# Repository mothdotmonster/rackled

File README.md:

# RACKLED

1U rackmount blinkenlights module

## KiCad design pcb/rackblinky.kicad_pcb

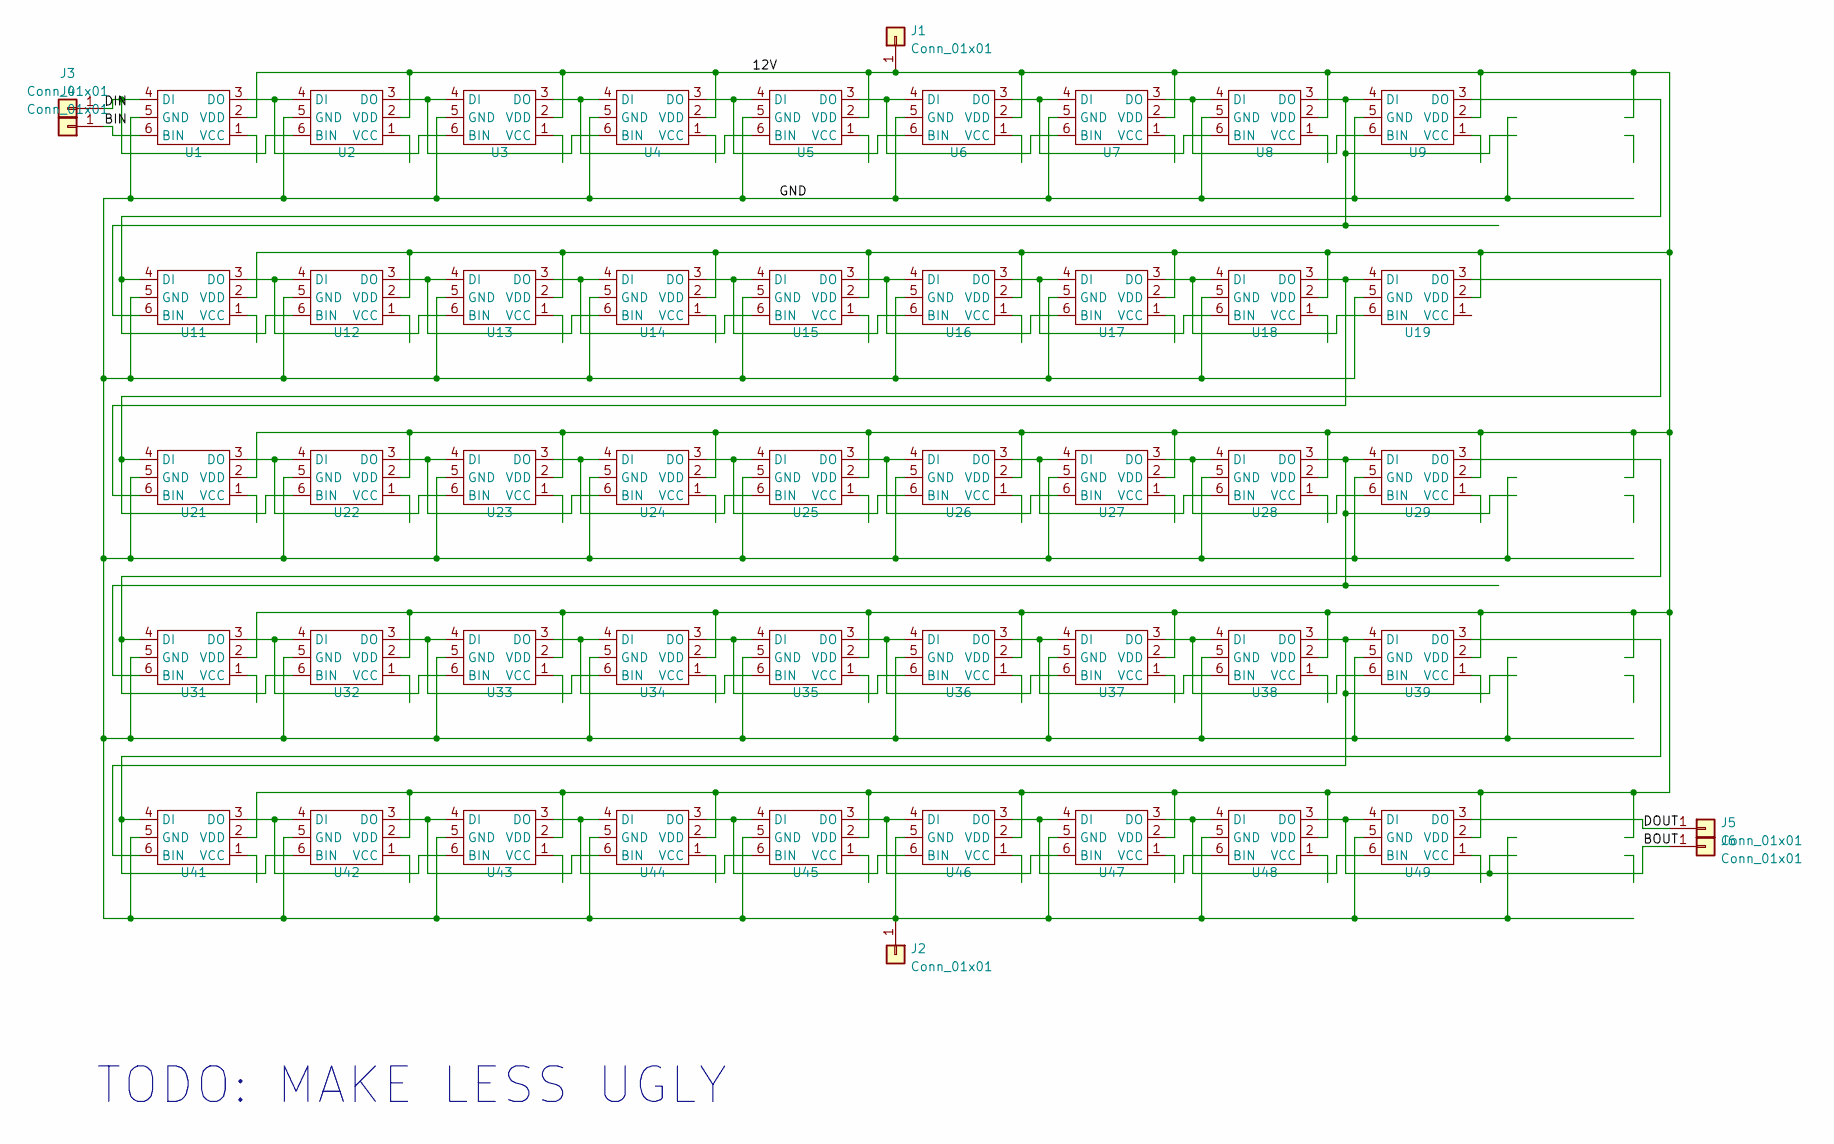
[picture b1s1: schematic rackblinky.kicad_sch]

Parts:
J1, J2: Conn_01x01; SolderWire-0.75sqmm_1x01_D1.25mm_OD2.3mm
J3, J4, J5, J6: Conn_01x01; SolderWirePad_1x01_SMD_1x2mm
U1, U2, U3, U4, U5, U6, U7, U8, U9, U11, U12, U13, U14, U15, U16, U17, U18, U19, U21, U22, U23, U24, U25, U26, U27, U28, U29, U31, U32, U33, U34, U35, U36, U37, U38, U39, U41, U42, U43, U44, U45, U46, U47, U48, U49: WS2815B; LED_RGB_5050-6; JLC C965559

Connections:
/12V: J1.1, U1.2 (VDD), U2.2 (VDD), U3.2 (VDD), U4.2 (VDD), U5.2 (VDD), U6.2 (VDD), U7.2 (VDD), U8.2 (VDD), U9.2 (VDD), U11.2 (VDD), U12.2 (VDD), U13.2 (VDD), U14.2 (VDD), U15.2 (VDD), U16.2 (VDD), U17.2 (VDD), U18.2 (VDD), U19.2 (VDD), U21.2 (VDD), U22.2 (VDD), U23.2 (VDD), U24.2 (VDD), U25.2 (VDD), U26.2 (VDD), U27.2 (VDD), U28.2 (VDD), U29.2 (VDD), U31.2 (VDD), U32.2 (VDD), U33.2 (VDD), U34.2 (VDD), U35.2 (VDD), U36.2 (VDD), U37.2 (VDD), U38.2 (VDD), U39.2 (VDD), U41.2 (VDD), U42.2 (VDD), U43.2 (VDD), U44.2 (VDD), U45.2 (VDD), U46.2 (VDD), U47.2 (VDD), U48.2 (VDD), U49.2 (VDD)
/BIN: J4.1, U1.6 (BIN)
/BOUT: J6.1, U48.3 (DO), U49.4 (DI)
/DIN: J3.1, U1.4 (DI), U2.6 (BIN)
/DOUT: J5.1, U49.3 (DO)
/GND: J2.1, U1.5 (GND), U2.5 (GND), U3.5 (GND), U4.5 (GND), U5.5 (GND), U6.5 (GND), U7.5 (GND), U8.5 (GND), U9.5 (GND), U11.5 (GND), U12.5 (GND), U13.5 (GND), U14.5 (GND), U15.5 (GND), U16.5 (GND), U17.5 (GND), U18.5 (GND), U19.5 (GND), U21.5 (GND), U22.5 (GND), U23.5 (GND), U24.5 (GND), U25.5 (GND), U26.5 (GND), U27.5 (GND), U28.5 (GND), U29.5 (GND), U31.5 (GND), U32.5 (GND), U33.5 (GND), U34.5 (GND), U35.5 (GND), U36.5 (GND), U37.5 (GND), U38.5 (GND), U39.5 (GND), U41.5 (GND), U42.5 (GND), U43.5 (GND), U44.5 (GND), U45.5 (GND), U46.5 (GND), U47.5 (GND), U48.5 (GND), U49.5 (GND)
unnamed: U1.3 (DO), U2.4 (DI), U3.6 (BIN)
unnamed: U2.3 (DO), U3.4 (DI), U4.6 (BIN)
unnamed: U3.3 (DO), U4.4 (DI), U5.6 (BIN)
unnamed: U4.3 (DO), U5.4 (DI), U6.6 (BIN)
unnamed: U5.3 (DO), U6.4 (DI), U7.6 (BIN)
unnamed: U6.3 (DO), U7.4 (DI), U8.6 (BIN)
unnamed: U7.3 (DO), U8.4 (DI), U9.6 (BIN)
unnamed: U11.3 (DO), U12.4 (DI), U13.6 (BIN)
unnamed: U9.3 (DO), U11.4 (DI), U12.6 (BIN)
unnamed: U8.3 (DO), U9.4 (DI), U11.6 (BIN)
unnamed: U12.3 (DO), U13.4 (DI), U14.6 (BIN)
unnamed: U13.3 (DO), U14.4 (DI), U15.6 (BIN)
unnamed: U14.3 (DO), U15.4 (DI), U16.6 (BIN)
unnamed: U15.3 (DO), U16.4 (DI), U17.6 (BIN)
unnamed: U16.3 (DO), U17.4 (DI), U18.6 (BIN)
unnamed: U17.3 (DO), U18.4 (DI), U19.6 (BIN)
unnamed: U18.3 (DO), U19.4 (DI), U21.6 (BIN)
unnamed: U19.3 (DO), U21.4 (DI), U22.6 (BIN)
unnamed: U21.3 (DO), U22.4 (DI), U23.6 (BIN)
unnamed: U22.3 (DO), U23.4 (DI), U24.6 (BIN)
unnamed: U23.3 (DO), U24.4 (DI), U25.6 (BIN)
unnamed: U24.3 (DO), U25.4 (DI), U26.6 (BIN)
unnamed: U25.3 (DO), U26.4 (DI), U27.6 (BIN)
unnamed: U26.3 (DO), U27.4 (DI), U28.6 (BIN)
unnamed: U27.3 (DO), U28.4 (DI), U29.6 (BIN)
unnamed: U28.3 (DO), U29.4 (DI), U31.6 (BIN)
unnamed: U29.3 (DO), U31.4 (DI), U32.6 (BIN)
unnamed: U31.3 (DO), U32.4 (DI), U33.6 (BIN)
unnamed: U32.3 (DO), U33.4 (DI), U34.6 (BIN)
unnamed: U33.3 (DO), U34.4 (DI), U35.6 (BIN)
unnamed: U34.3 (DO), U35.4 (DI), U36.6 (BIN)
unnamed: U35.3 (DO), U36.4 (DI), U37.6 (BIN)
unnamed: U36.3 (DO), U37.4 (DI), U38.6 (BIN)
unnamed: U37.3 (DO), U38.4 (DI), U39.6 (BIN)
unnamed: U38.3 (DO), U39.4 (DI), U41.6 (BIN)
unnamed: U39.3 (DO), U41.4 (DI), U42.6 (BIN)
unnamed: U41.3 (DO), U42.4 (DI), U43.6 (BIN)
unnamed: U42.3 (DO), U43.4 (DI), U44.6 (BIN)
unnamed: U43.3 (DO), U44.4 (DI), U45.6 (BIN)
unnamed: U44.3 (DO), U45.4 (DI), U46.6 (BIN)
unnamed: U45.3 (DO), U46.4 (DI), U47.6 (BIN)
unnamed: U46.3 (DO), U47.4 (DI), U48.6 (BIN)
unnamed: U47.3 (DO), U48.4 (DI), U49.6 (BIN)

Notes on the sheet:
TODO: MAKE LESS UGLY

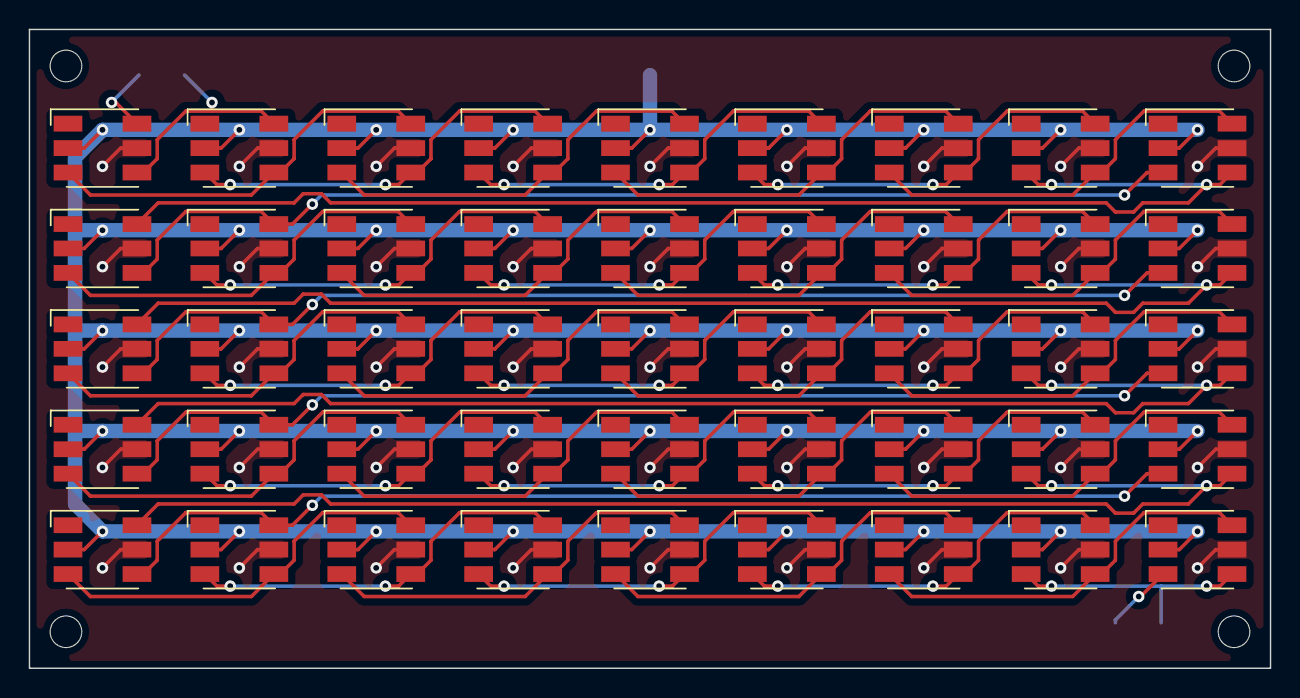
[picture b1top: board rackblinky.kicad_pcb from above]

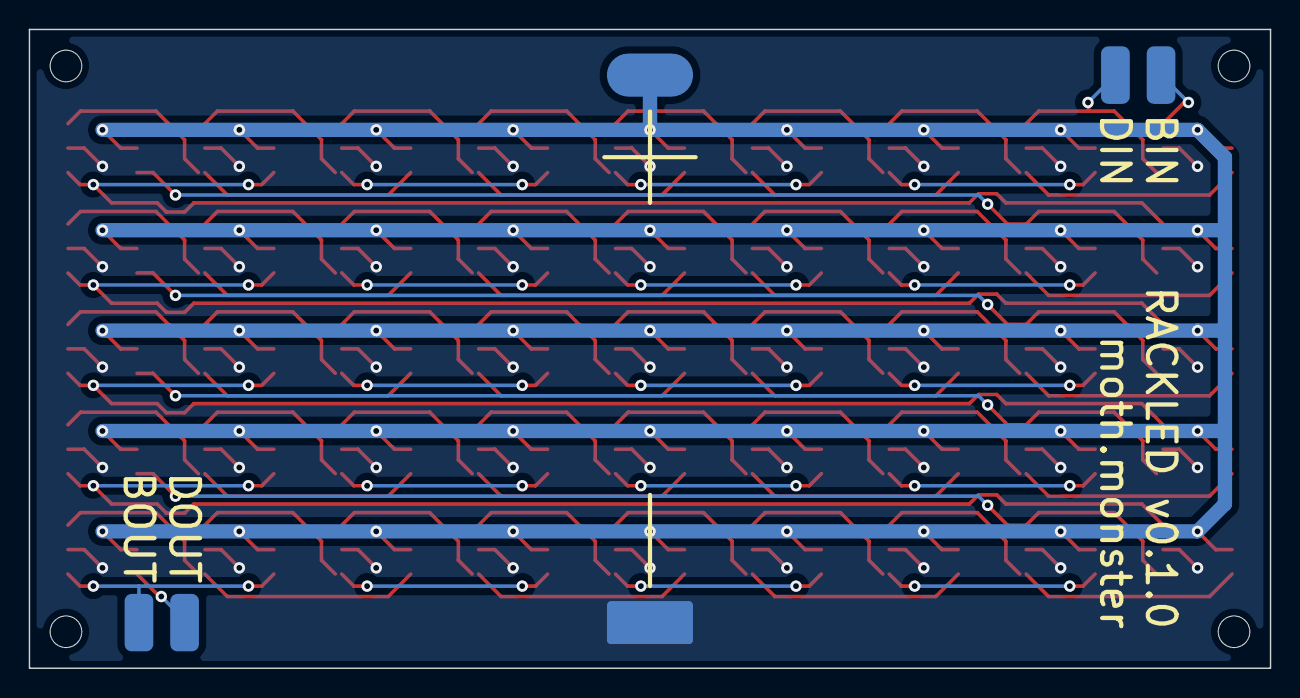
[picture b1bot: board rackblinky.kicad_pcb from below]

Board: 2 copper layers, 86.4 x 44.4 mm, 51 parts (6 on the bottom side), 49 nets.

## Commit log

2022-05-10 add case files
2022-05-10 add pcb files
2022-05-10 add images
2022-05-11 new case design files
2022-05-11 new image
2022-05-11 new images
